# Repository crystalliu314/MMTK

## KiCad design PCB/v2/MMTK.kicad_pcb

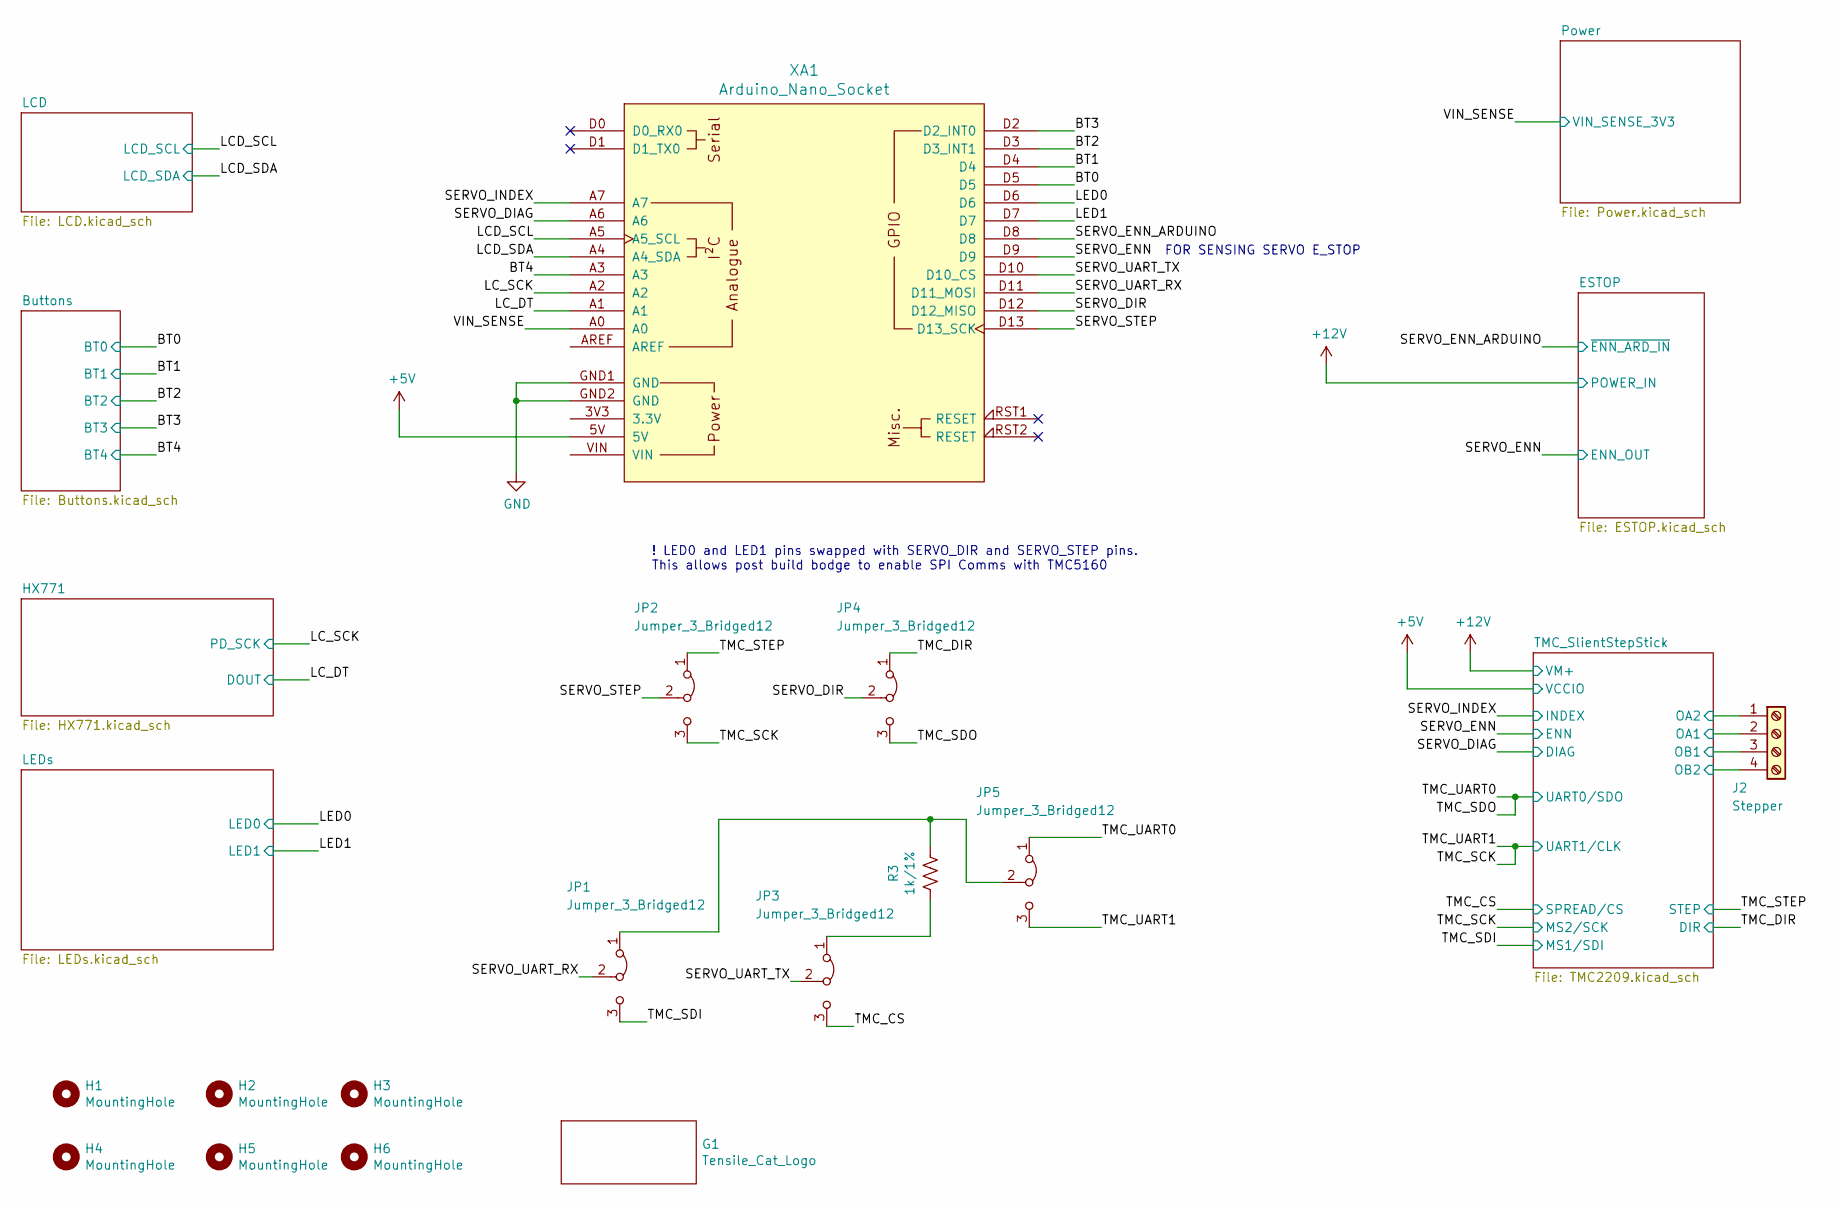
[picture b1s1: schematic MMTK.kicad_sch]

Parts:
G1: Tensile_Cat_Logo; Tensile Cat
H1, H2, H3, H4, H5, H6: MountingHole; MountingHole_4mm
J2: Stepper; TerminalBlock_RND_205-00289_1x04_P5.08mm_Horizontal
JP1, JP2, JP3, JP4, JP5: Jumper_3_Bridged12; SolderJumper-3_P1.3mm_Bridged12_Pad1.0x1.5mm_NumberLabels
R3: 1k/1%; R_0603_1608Metric
XA1: Arduino_Nano_Socket

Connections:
+5V: XA1.5V; also elsewhere on the board
/BT0: XA1.D5; also elsewhere on the board
/BT1: XA1.D4; also elsewhere on the board
/BT2: XA1.D3 (D3_INT1); also elsewhere on the board
/BT3: XA1.D2 (D2_INT0); also elsewhere on the board
/BT4: XA1.A3; also elsewhere on the board
/LCD_SCL: XA1.A5 (A5_SCL); also elsewhere on the board
/LCD_SDA: XA1.A4 (A4_SDA); also elsewhere on the board
/LC_DT: XA1.A1; also elsewhere on the board
/LC_SCK: XA1.A2; also elsewhere on the board
/LED0: XA1.D6; also elsewhere on the board
/LED1: XA1.D7; also elsewhere on the board
/SERVO_DIAG: XA1.A6; also elsewhere on the board
/SERVO_DIR: JP4.2 (C), XA1.D12 (D12_MISO)
/SERVO_ENN: XA1.D9; also elsewhere on the board
/SERVO_ENN_ARDUINO: XA1.D8; also elsewhere on the board
/SERVO_INDEX: XA1.A7; also elsewhere on the board
/SERVO_STEP: JP2.2 (C), XA1.D13 (D13_SCK)
/SERVO_UART_RX: JP1.2 (C), XA1.D11 (D11_MOSI)
/SERVO_UART_TX: JP3.2 (C), XA1.D10 (D10_CS)
/TMC_CS: JP3.3 (B); also elsewhere on the board
/TMC_DIR: JP4.1 (A); also elsewhere on the board
/TMC_SCK: JP2.3 (B), JP5.3 (B); also elsewhere on the board
/TMC_SDI: JP1.3 (B); also elsewhere on the board
/TMC_SDO: JP4.3 (B), JP5.1 (A); also elsewhere on the board
/TMC_STEP: JP2.1 (A); also elsewhere on the board
/TMC_SlientStepStick/OA1: J2.2; also elsewhere on the board
/TMC_SlientStepStick/OA2: J2.1; also elsewhere on the board
/TMC_SlientStepStick/OB1: J2.3; also elsewhere on the board
/TMC_SlientStepStick/OB2: J2.4; also elsewhere on the board
/VIN_SENSE: XA1.A0; also elsewhere on the board
GND: XA1.GND1 (GND), XA1.GND2 (GND); also elsewhere on the board
unnamed: JP1.1 (A), JP5.2 (C), R3.1
unnamed: JP3.1 (A), R3.2

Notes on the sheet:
! LED0 and LED1 pins swapped with SERVO_DIR and SERVO_STEP pins. This allows post build bodge to enable SPI Comms with TMC5160
FOR SENSING SERVO E_STOP

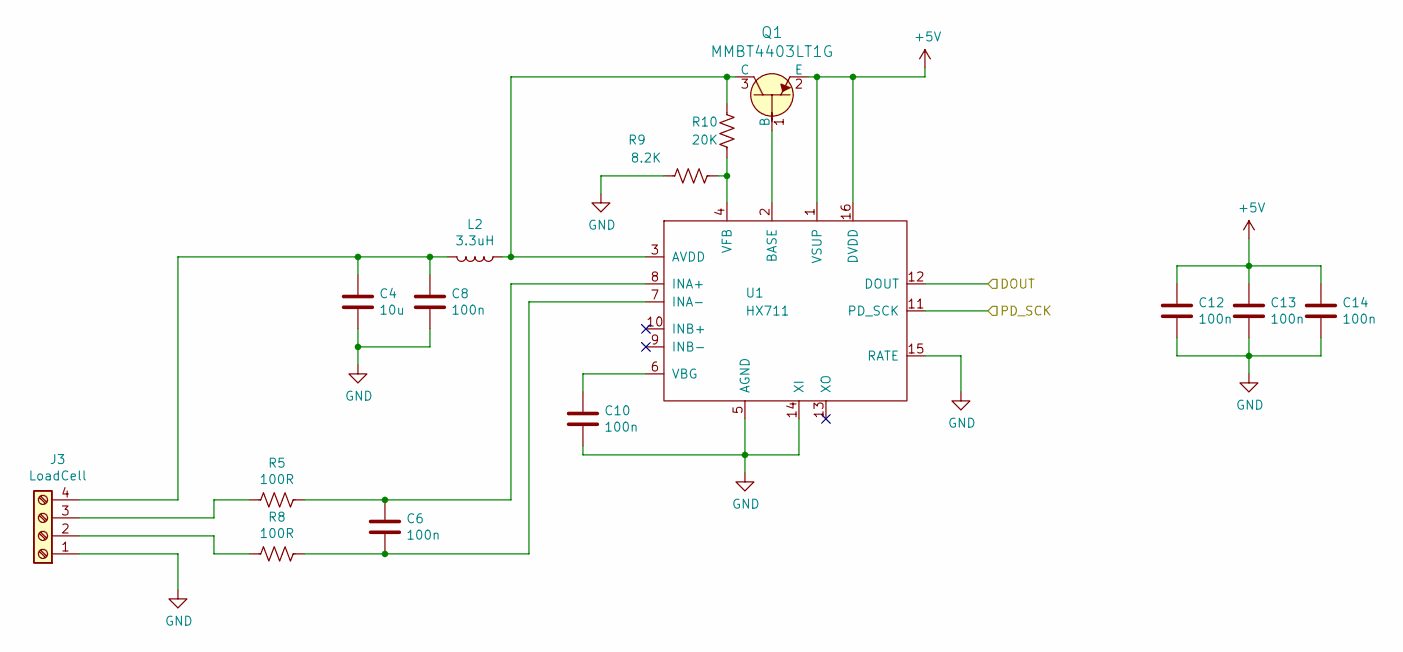
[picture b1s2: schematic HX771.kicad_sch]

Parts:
C4: 10u; C_1206_3216Metric
C6, C8, C10, C12, C13, C14: 100n; C_0603_1608Metric
J3: LoadCell; TerminalBlock_Phoenix_PT-1,5-4-3.5-H_1x04_P3.50mm_Horizontal
L2: 3.3uH; L_0805_2012Metric
Q1: MMBT4403LT1G; SOT-23-3; MPN MMBT4403LT1G; Digi-Key_PN MMBT4403LT1GOSCT-ND
R5, R8: 100R; R_0603_1608Metric
R9: 8.2K; R_0603_1608Metric
R10: 20K; R_0603_1608Metric
U1: HX711; SOIC-16_3.9x9.9mm_P1.27mm

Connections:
+5V: C12.1, C13.1, C14.1, Q1.2 (E), U1.1 (VSUP), U1.16 (DVDD); also elsewhere on the board
/LC_DT: U1.12 (DOUT); also elsewhere on the board
/LC_SCK: U1.11 (PD_SCK); also elsewhere on the board
GND: C4.2, C8.2, C10.2, C12.2, C13.2, C14.2, J3.1, R9.1, U1.5 (AGND), U1.14 (XI), U1.15 (RATE); also elsewhere on the board
unnamed: C4.1, C8.1, J3.4, L2.2
unnamed: C6.1, R5.1, U1.8 (INA+)
unnamed: C6.2, R8.1, U1.7 (INA-)
unnamed: C10.1, U1.6 (VBG)
unnamed: J3.2, R8.2
unnamed: J3.3, R5.2
unnamed: L2.1, Q1.3 (C), R10.2, U1.3 (AVDD)
unnamed: Q1.1 (B), U1.2 (BASE)
unnamed: R9.2, R10.1, U1.4 (VFB)

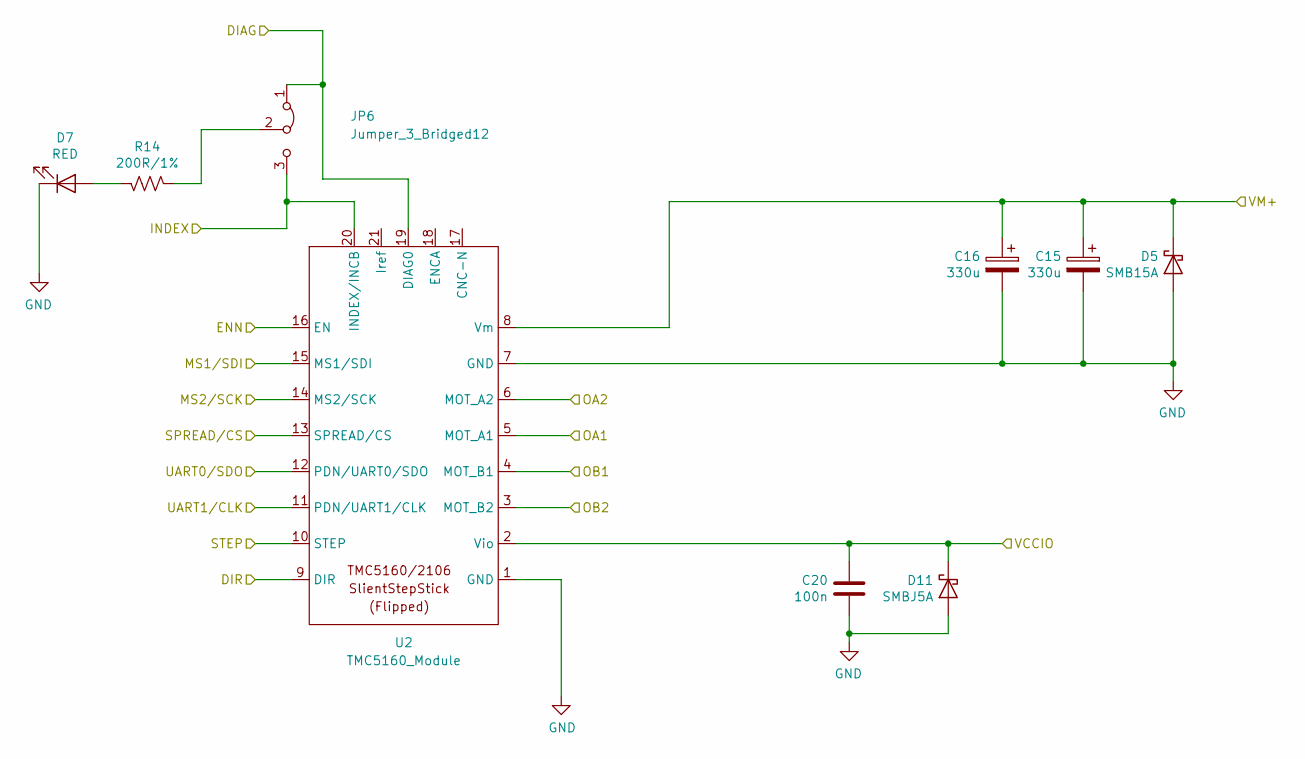
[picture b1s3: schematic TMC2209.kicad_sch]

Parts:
C15, C16: 330u; CP_Elec_10x10
C20: 100n; C_0603_1608Metric
D5: SMB15A; D_SMB
D7: RED; LED_0603_1608Metric
D11: SMBJ5A; D_SMB
JP6: Jumper_3_Bridged12; SolderJumper-3_P1.3mm_Bridged12_Pad1.0x1.5mm_NumberLabels
R14: 200R/1%; R_0603_1608Metric
U2: TMC5160_Module; TMCC2209_Module_copy

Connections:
+5V: C20.1, D11.1 (K), U2.2 (Vio); also elsewhere on the board
+12V: C15.1, C16.1, D5.1 (K), U2.8 (Vm); also elsewhere on the board
/SERVO_DIAG: JP6.1 (A), U2.19 (DIAG0); also elsewhere on the board
/SERVO_ENN: U2.16 (EN); also elsewhere on the board
/SERVO_INDEX: JP6.3 (B), U2.20 (INDEX/INCB); also elsewhere on the board
/TMC_CS: U2.13 (SPREAD/CS); also elsewhere on the board
/TMC_DIR: U2.9 (DIR); also elsewhere on the board
/TMC_SCK: U2.11 (PDN/UART1/CLK), U2.14 (MS2/SCK); also elsewhere on the board
/TMC_SDI: U2.15 (MS1/SDI); also elsewhere on the board
/TMC_SDO: U2.12 (PDN/UART0/SDO); also elsewhere on the board
/TMC_STEP: U2.10 (STEP); also elsewhere on the board
/TMC_SlientStepStick/OA1: U2.5 (MOT_A1); also elsewhere on the board
/TMC_SlientStepStick/OA2: U2.6 (MOT_A2); also elsewhere on the board
/TMC_SlientStepStick/OB1: U2.4 (MOT_B1); also elsewhere on the board
/TMC_SlientStepStick/OB2: U2.3 (MOT_B2); also elsewhere on the board
GND: C15.2, C16.2, C20.2, D5.2 (A), D7.1 (K), D11.2 (A), U2.1 (GND), U2.7 (GND); also elsewhere on the board
unnamed: D7.2 (A), R14.1
unnamed: JP6.2 (C), R14.2

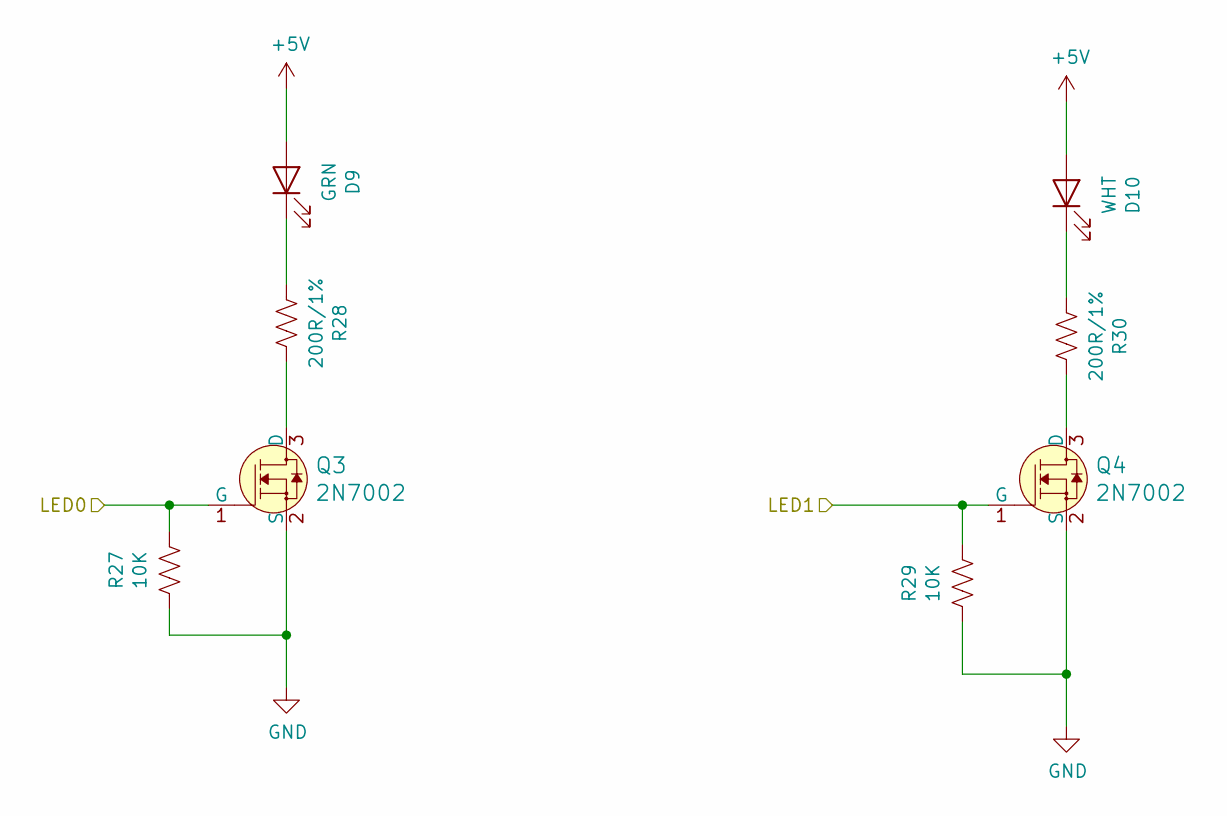
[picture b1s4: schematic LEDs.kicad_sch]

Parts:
D9: GRN; LED_0603_1608Metric
D10: WHT; LED_0603_1608Metric
Q3, Q4: 2N7002; SOT-23-3; MPN 2N7002; Digi-Key_PN 2N7002NCT-ND
R27, R29: 10K; R_0603_1608Metric
R28, R30: 200R/1%; R_0603_1608Metric

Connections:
+5V: D9.2 (A), D10.2 (A); also elsewhere on the board
/LED0: Q3.1 (G), R27.1; also elsewhere on the board
/LED1: Q4.1 (G), R29.1; also elsewhere on the board
GND: Q3.2 (S), Q4.2 (S), R27.2, R29.2; also elsewhere on the board
unnamed: D9.1 (K), R28.2
unnamed: D10.1 (K), R30.2
unnamed: Q3.3 (D), R28.1
unnamed: Q4.3 (D), R30.1

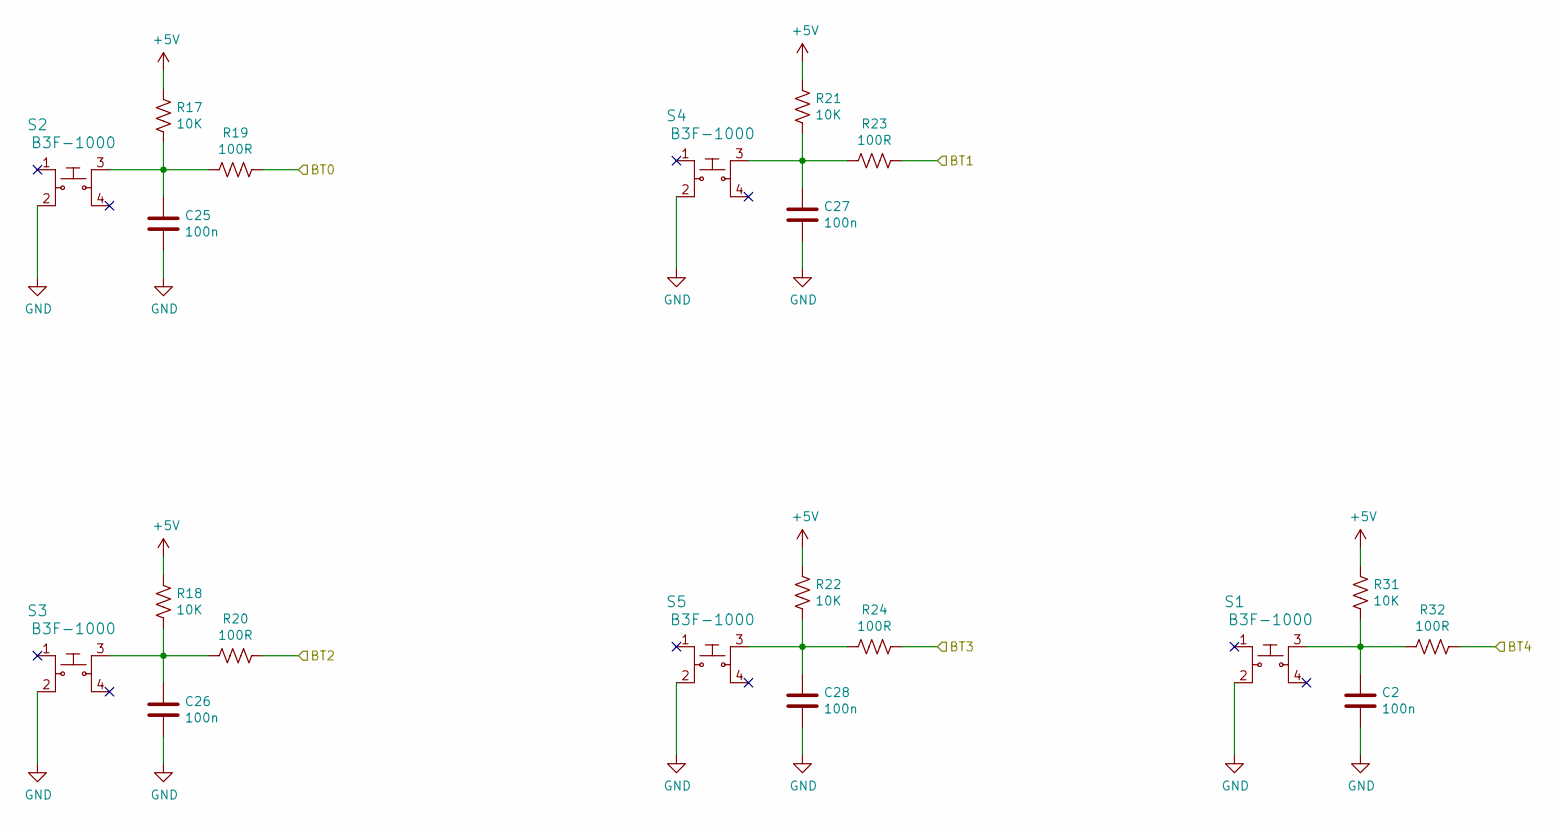
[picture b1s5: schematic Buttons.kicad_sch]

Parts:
C2, C25, C26, C27, C28: 100n; C_0603_1608Metric
R17, R18, R21, R22, R31: 10K; R_0603_1608Metric
R19, R20, R23, R24, R32: 100R; R_0603_1608Metric
S1, S2, S3, S4, S5: B3F-1000; Switch_Tactile_SMD_6x6mm; MPN B3F-1000; Digi-Key_PN SW400-ND

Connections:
+5V: R17.1, R18.1, R21.1, R22.1, R31.1; also elsewhere on the board
/BT0: R19.1; also elsewhere on the board
/BT1: R23.1; also elsewhere on the board
/BT2: R20.1; also elsewhere on the board
/BT3: R24.1; also elsewhere on the board
/BT4: R32.1; also elsewhere on the board
GND: C2.2, C25.2, C26.2, C27.2, C28.2, S1.2, S2.2, S3.2, S4.2, S5.2; also elsewhere on the board
unnamed: C2.1, R31.2, R32.2, S1.3
unnamed: C25.1, R17.2, R19.2, S2.3
unnamed: C26.1, R18.2, R20.2, S3.3
unnamed: C27.1, R21.2, R23.2, S4.3
unnamed: C28.1, R22.2, R24.2, S5.3

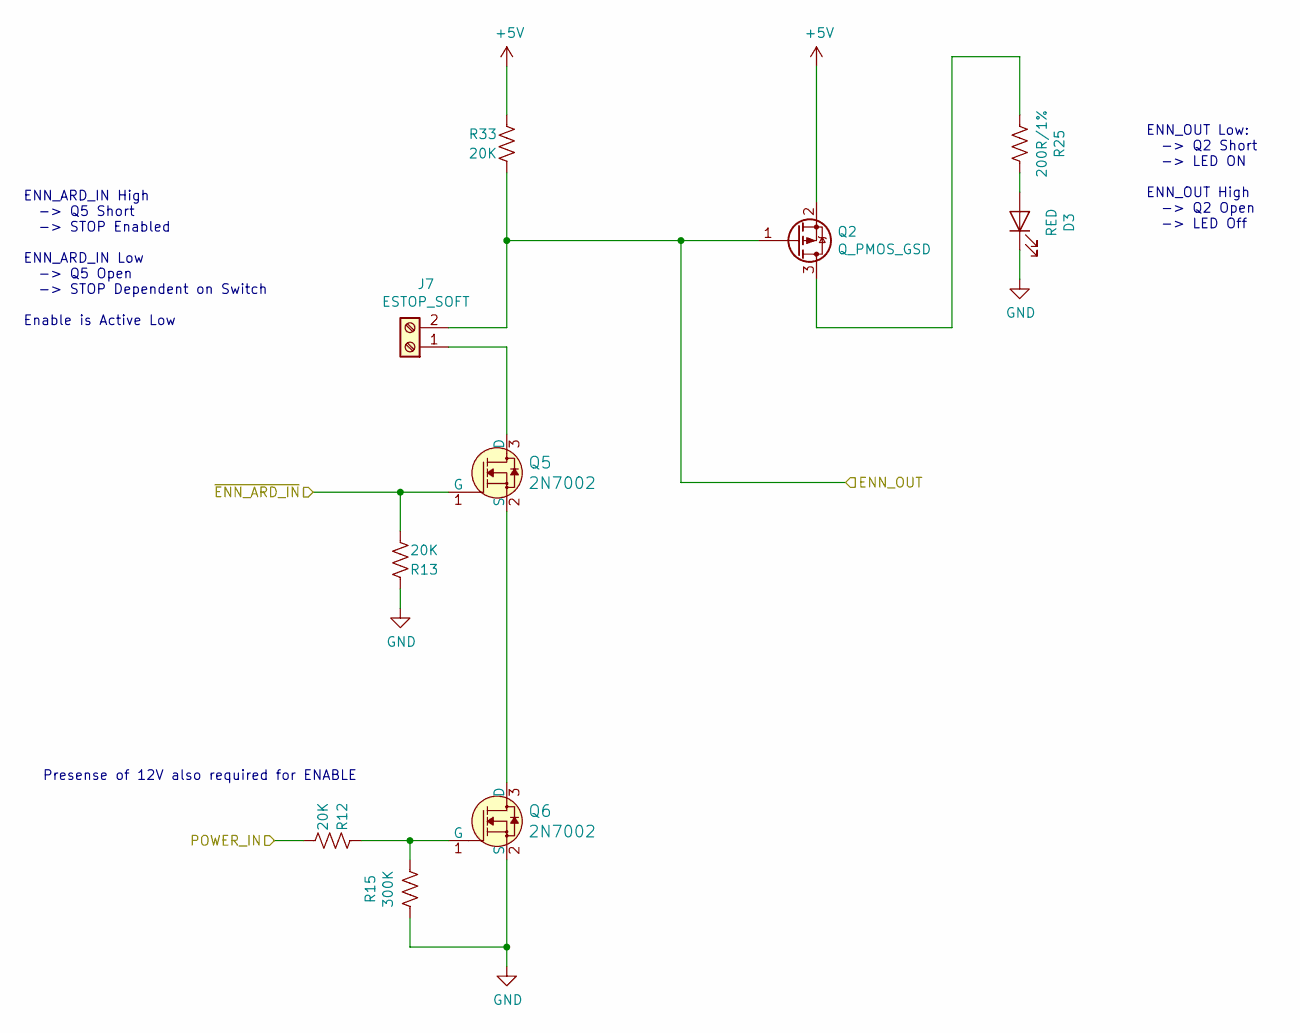
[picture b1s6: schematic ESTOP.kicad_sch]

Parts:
D3: RED; LED_0603_1608Metric
J7: ESTOP_SOFT; TerminalBlock_Phoenix_PT-1,5-2-3.5-H_1x02_P3.50mm_Horizontal
Q2: Q_PMOS_GSD; SOT-23
Q5, Q6: 2N7002; SOT-23-3; MPN 2N7002; Digi-Key_PN 2N7002NCT-ND
R12, R13, R33: 20K; R_0603_1608Metric
R15: 300K; R_0603_1608Metric
R25: 200R/1%; R_0603_1608Metric

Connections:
+5V: Q2.2 (S), R33.2; also elsewhere on the board
+12V: R12.1; also elsewhere on the board
/SERVO_ENN: J7.2, Q2.1 (G), R33.1; also elsewhere on the board
/SERVO_ENN_ARDUINO: Q5.1 (G), R13.1; also elsewhere on the board
GND: D3.1 (K), Q6.2 (S), R13.2, R15.2; also elsewhere on the board
unnamed: D3.2 (A), R25.1
unnamed: J7.1, Q5.3 (D)
unnamed: Q2.3 (D), R25.2
unnamed: Q5.2 (S), Q6.3 (D)
unnamed: Q6.1 (G), R12.2, R15.1

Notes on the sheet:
Presense of 12V also required for ENABLE
ENN_ARD_IN High -> Q5 Short -> STOP Enabled ENN_ARD_IN Low -> Q5 Open -> STOP Dependent on Switch Enable is Active Low
ENN_OUT Low: -> Q2 Short -> LED ON ENN_OUT High -> Q2 Open -> LED Off

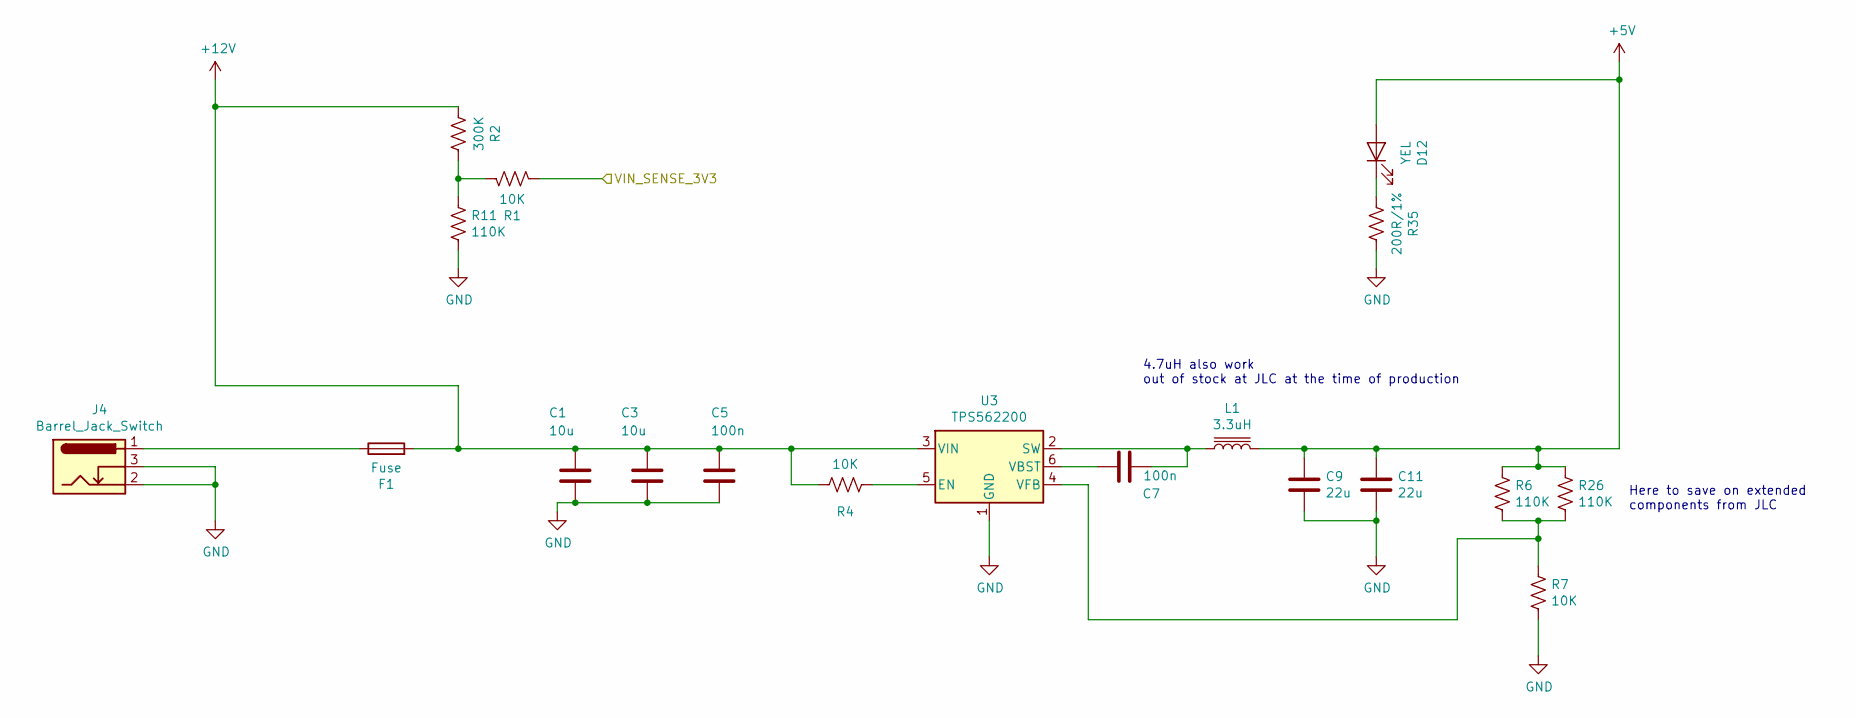
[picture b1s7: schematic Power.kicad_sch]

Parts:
C1, C3: 10u; C_1206_3216Metric
C5, C7: 100n; C_0603_1608Metric
C9, C11: 22u; C_0805_2012Metric
D12: YEL; LED_0603_1608Metric
F1: Fuse; Fuse_2920_7451Metric
J4: Barrel_Jack_Switch; BarrelJack_Horizontal
L1: 3.3uH; L_Bourns_SRP7028A_7.3x6.6mm
R1, R4, R7: 10K; R_0603_1608Metric
R2: 300K; R_0603_1608Metric
R6, R11, R26: 110K; R_0603_1608Metric
R35: 200R/1%; R_0603_1608Metric
U3: TPS562200; SOT-23-6

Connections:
+5V: C9.1, C11.1, D12.2 (A), L1.2, R6.1, R26.1; also elsewhere on the board
+12V: C1.1, C3.1, C5.1, F1.2, R2.2, R4.1, U3.3 (VIN); also elsewhere on the board
/VIN_SENSE: R1.1; also elsewhere on the board
GND: C1.2, C3.2, C5.2, C9.2, C11.2, J4.2, J4.3, R7.2, R11.2, R35.1, U3.1 (GND); also elsewhere on the board
unnamed: C7.1, L1.1, U3.2 (SW)
unnamed: C7.2, U3.6 (VBST)
unnamed: D12.1 (K), R35.2
unnamed: F1.1, J4.1
unnamed: R1.2, R2.1, R11.1
unnamed: R4.2, U3.5 (EN)
unnamed: R6.2, R7.1, R26.2, U3.4 (VFB)

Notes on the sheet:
4.7uH also work out of stock at JLC at the time of production
Here to save on extended components from JLC

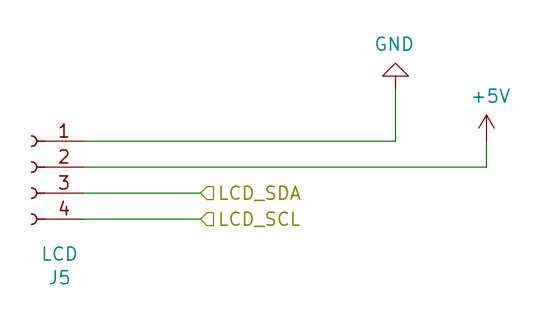
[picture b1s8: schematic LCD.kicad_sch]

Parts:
J5: LCD; PinSocket_1x04_P2.54mm_Horizontal

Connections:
+5V: J5.2; also elsewhere on the board
/LCD_SCL: J5.4; also elsewhere on the board
/LCD_SDA: J5.3; also elsewhere on the board
GND: J5.1; also elsewhere on the board

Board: 4 copper layers, 97 parts (2 on the bottom side), 67 nets, no tracks yet.

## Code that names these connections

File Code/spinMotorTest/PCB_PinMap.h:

// Pin mapping for tensile cat PCB
#pragma once

#define LOADCELL_DATA A1
#define LOADCELL_CLOCK A2
#define SERVO_SPEED A3
#define SERVO_DIAG A4
#define SERVO_INDEX A5

#define BT_FW 2
#define BT_BK 3
#define BT_TARE 4
#define BT_START 5

#define SERVO_DIR 6
#define SERVO_STEP 7
#define SERVO_ENN 8
#define SERVO_ENN_STOP 9
#define SERVO_TX 10
#define SERVO_RX 11

#define LED0 12
#define LED1 13

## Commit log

2020-12-08 Test
2020-12-08 Added code to just spin motor
2020-12-11 Added button control direction
    use botton to control direction
    this is a bit sketch
2020-12-12 Add PCB Files
    Added PCB files, preliinary for now
2020-12-17 WIP qa codes
2020-12-17 still working on it
2020-12-23 Code Mostly Done
    Leaving code in QA folder for now, official code will be released later
2020-12-23 Forgor to copy over files
    Copied over proper code from platform IO
    Now code is actrually updated
2020-12-23 Bug fixes
    Bugs mostly ironed out i think,
    Firmware done for now
2020-12-24 started on MMTK_UI
2020-12-25 Update MockupSerial.pde
    wip
2020-12-27 wip
    working on it slowly
2020-12-27 wip
    still working on it
2020-12-28 wip
    saving progress
2020-12-29 WIP
    Continue work on UI,
    Some changes to firmware to add liip speed limitation for async operation
2020-12-30 wip
    update save file
2020-12-31 dialogue for serial port
    added dialogue to ask for user which serial port to use
2021-01-01 updated ui and code
    more work
    correction for machine deflection is in the works but not done yet
2021-01-01 update hardlink (local thing)
2021-01-02 Added Exported Apps
2021-01-03 Update .gitignore
    Added gitignore for exported apps
2021-01-06 updated ui with a bit of controls
2021-01-24 Clean up
    Removed reference code for processing and old spinMotorTest
2021-01-24 update gitignore
    update gitignore to not ignore exe
2021-01-24 remote export, zip file
2021-01-24 make window bigger
    now is 1366 x 768
2021-01-24 Fix typos
    Displacement and mm/min
2021-01-24 Edit banner and fix typos
2021-01-24 sdfixa stydfdd
2021-02-02 control frame updates; added 5kg calibration
2021-02-06 Serial port bug fix
2021-02-07 Move app into its own folder
2021-02-08 Upload exported executable
2021-02-08 Upload software for MacOS
2021-02-08 added version number
2021-02-17 Persist Calibration by EEPROM
    We now store calibration with EEPROM.
    Default values will be used if EEPROM is not initialized.
    Changed calibration code to avgerage loadcell values
2021-02-17 Release code with updated spring scale calibration
2021-02-17 redundant
2021-02-17 Updated UI with separate calibration file
    Updated UI with separate calibration file in case of accidental click on calibration button during normal use
2021-02-17 Exported calibration UI for 64bit
2021-02-17 Removed unrelated data logs
2021-02-17 Update default speed to 50mm/min
2021-04-06 .STEP file update
2021-04-13 PCB Production file name update
2021-05-18 Move to position
    Arduino updated press start move to position
2021-05-18 UI send wave pattern
    Send position and velocity through serial for certain wave form input
2021-05-25 Update patterns for stretcher code in UI
2021-05-25 Update plot
2021-05-25 remove exe
2021-06-16 Add PDF, fix gitignore
    gitignore was too broad and removed lib files for kicad. That is fix.
    updated pdf schematics to include latest changes (not yet manufacturered)
2022-05-23 reorg files
2022-05-24 Initial V2 Work, WIP
    - Add symbol and footprint for TMC2209 SlientStepStick Breakout
    - Change Arduino to Nano in Schematic
    - Change ESTOP circuit to be an actual loop
2022-05-24 Tore up PCB
    Tore up PCB, just need to reroute whole thing easier than trying to reuse existing.
2022-05-24 Estop Notes
    Added annotation for notes about estop on schematic
2022-05-24 Add 12V to ENN Loop
    Added 12v detection to ENN loop, so EN on tmc would be high if 12v not present but 5v is.
2022-09-30 Opened in KiCad 6
    Imported libs and stuff for KiCad 6, working on it now
2022-10-12 WIP updated symbols for tmc5106
    Updated footprint for tmc5106,
    need to check how motor wiring is done, might be wired up stupid before and that's gonna be sad
2022-10-17 Figured Out Motor Wiring
    Updated motor wiring, naming on slient step stick is the same as tmc chips itself.
    Phrases are A and B and 1/2 are the wires from the same phrase.
2022-10-17 Updating PCB now
    updating pcb now, schematic is done now. Mostly just PCB now
2023-04-01 Update PCB, sync with git
2024-06-25 MMTK PCB Update
2025-04-05 update and upgrade to kicad9
